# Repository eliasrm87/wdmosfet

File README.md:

# WDSSR

WDSSR is a low side DC Mosfet based SSR board designed to drive resistive loads with and integrated watchdog able to detect some of the more common faults, report and protect it self from fire hazard.

## Watchdog capabilities

The integrated, fully analog, free of firmware, watchdog has the ability to detect:
 - Broken cable
 - Shorted switching Mosfet

For any of the cases described above, the board will “open” the series safety Mosfet and will trigger an alarm open collector signal for the control system to take further action, reducing the fire hazard resulting from an uncontrolled thermal runaway or defective wiring.

## Simplified principle of operation

 - The resistive load pulls the Drain to VCC
 - When Control is pulled up, the MOSFET “closes”, pulling its Drain close GND
 - Comparing voltages at Drain and Gate, a faulty MOSFET can be detected

| Gate | Drain | Result                                 |
| ---- | ----- | -------------------------------------- |
| Low  | Low   | Faulty - Source and drain  shorted     |
| High | Low   | Normal - ON                            |
| Low  | High  | Normal - OFF                           |
| High | High  | Faulty – Open or gate shorted to drain |

## Bill Of Material

You could consider using the included [Interactive Bill of Material](https://htmlpreview.github.io/?https://raw.githubusercontent.com/eliasrm87/wdssr/master/bom/WDSSR_ibom.html) for a better assembly experience.

|Qty|Reference(s)              |Value           |Part Number                                               |LCSC Part #                                                                  |
|---|--------------------------|----------------|----------------------------------------------------------|-----------------------------------------------------------------------------|
|1  |C1                        |100n            |                                                          |C14663                                                                       |
|1  |C2                        |1u              |                                                          |C15849                                                                       |
|1  |C3                        |10n             |                                                          |C14663                                                                       |
|1  |D1                        |ABS6            |                                                          |C169532                                                                      |
|2  |D2, D4                    |BAV70           |                                                          |C68978                                                                       |
|1  |D3                        |LED_G           |                                                          |C72043                                                                       |
|1  |D5                        |LED_R           |                                                          |C2286                                                                        |
|1  |D6                        |D_Zener         |MM3Z12VB                                                  |C891576                                                                      |
|1  |J1                        |B2B-XH-A(LF)(SN)|B3B-XH-AM(LF)(SN)                                         |C161870                                                                      |
|1  |J2                        |1714968         |1714968                                                   |C95692                                                                       |
|1  |J3                        |Conn_01x02_Male |                                                          |C160332                                                                      |
|2  |Q1, Q2                    |IRFR7440TRPBF   |IRFR7440TRPBF                                             |C97244                                                                       |
|2  |Q3, Q4                    |BC846B,215      |                                                          |C87062                                                                       |
|2  |R1, R12                   |2K              |                                                          |C21190                                                                       |
|6  |R2, R5, R11, R14, R15, R16|10K             |                                                          |C25804                                                                       |
|5  |R3, R7, R8, R9, R13       |100K            |                                                          |C25803                                                                       |
|1  |R4                        |1K              |                                                          |C21190                                                                       |
|2  |R6, R17                   |100             |                                                          |C22775                                                                       |
|1  |U1                        |LM358DT         |                                                          |C9418                                                                        |
|1  |U2                        |TLP185          |                                                          |C7240                                                                        |

## Limitations

This design is not bullet proof and may fail to achieve it’s objective in certain cases:
 - The series safety Mosfet may overheat and fail exactly at the same time as the switching Mosfet
 - It is only tested and verified to work with resistive loads, like heaters. Uses of this design with inductive loads has not been yet tested and may need hardware modifications

### Front

### Back

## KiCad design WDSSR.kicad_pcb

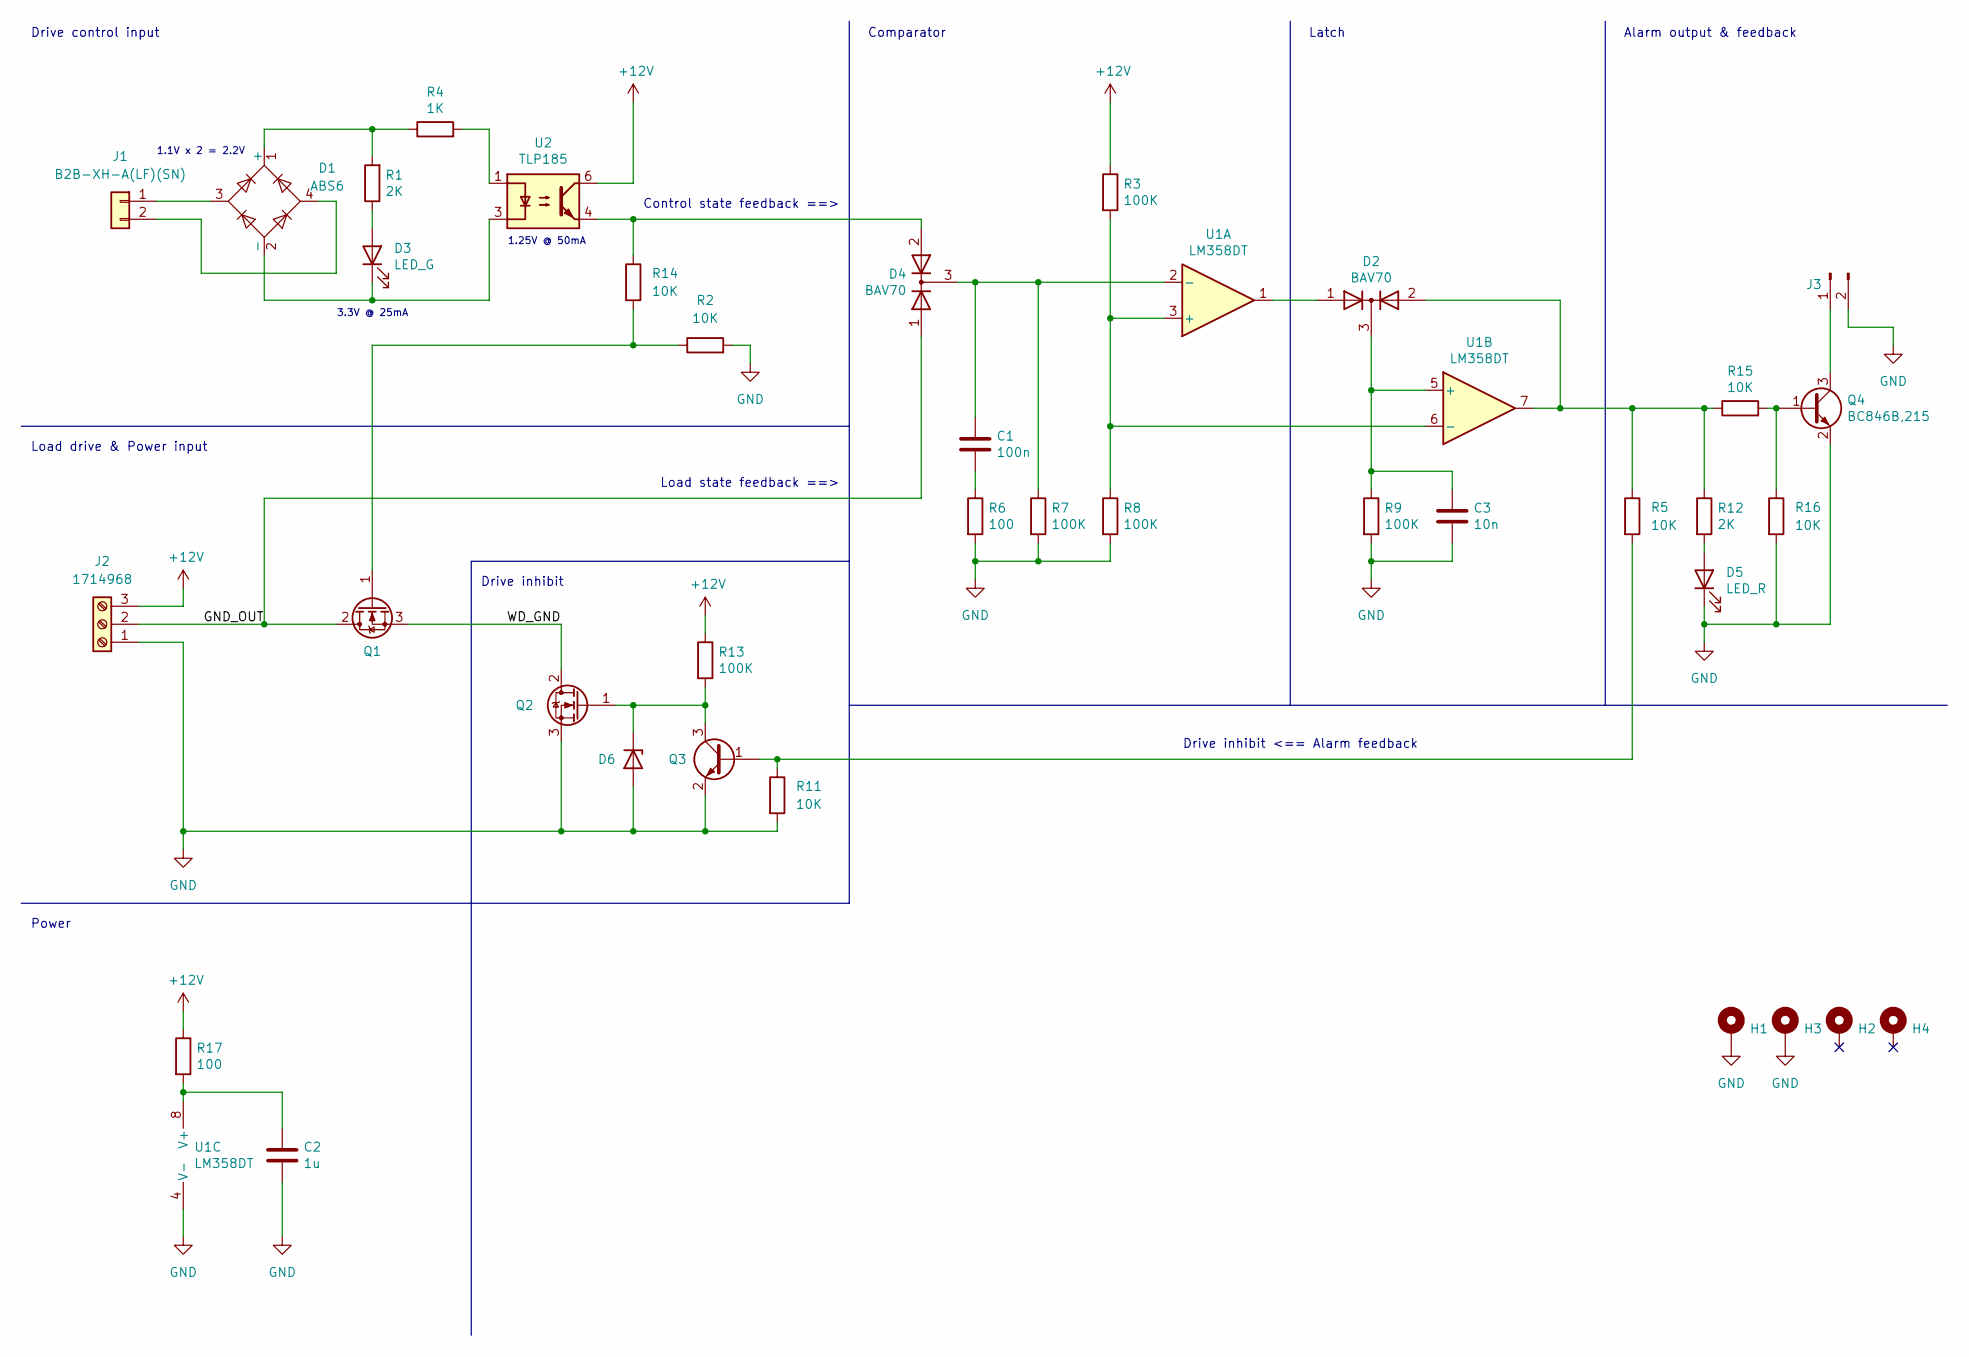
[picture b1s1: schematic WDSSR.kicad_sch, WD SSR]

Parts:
C1: 100n; C_0603_1608Metric_Pad1.08x0.95mm_HandSolder; Manufacturer_Part_Number CC0603KRX7R9BB104; LCSC Part # C14663
C2: 1u; C_0603_1608Metric_Pad1.08x0.95mm_HandSolder; Manufacturer_Part_Number CL10A105KB8NNNC; LCSC Part # C15849
C3: 10n; C_0603_1608Metric_Pad1.08x0.95mm_HandSolder; Manufacturer_Part_Number CC0603KRX7R9BB104; LCSC Part # C14663
D1: ABS6; Diode_Bridge_Diotec_ABS; Manufacturer_Part_Number ABS6-10; LCSC Part # C169532
D2, D4: BAV70; SOT-23; Manufacturer_Part_Number BAV70; LCSC Part # C68978
D3: LED_G; LED_0603_1608Metric_Pad1.05x0.95mm_HandSolder; Manufacturer_Part_Number 19-217/GHC-YR1S2/3T; LCSC Part # C72043
D5: LED_R; LED_0603_1608Metric_Pad1.05x0.95mm_HandSolder; Manufacturer_Part_Number KT-0603R; LCSC Part # C2286
D6: D_Zener; D_SOD-323F; Part Number MM3Z12VB; LCSC Part # C891576
H1, H2, H3, H4: MountingHole; MountingHole_3.2mm_M3_ISO7380_Pad; Manufacturer_Part_Number DNP
J1: B2B-XH-A(LF)(SN); LIB_B2B-XH-A(LF)(SN); Part Number B3B-XH-AM(LF)(SN); LCSC Part # C161870
J2: 1714968; SHDR3W90P0X635_1X3_1905X1250X2150P; Part Number 1714968; LCSC Part # C95692
J3: Conn_01x02_Male; PinHeader_1x02_P2.54mm_Vertical; Manufacturer_Part_Number RE-H022TD-1190(LF)(SN); LCSC Part # C160332
Q1, Q2: IRFR7440TRPBF; TO-252-2; Part Number IRFR7440TRPBF; LCSC Part # C97244
Q3, Q4: BC846B,215; SOT-23; Manufacturer_Part_Number BC846B,215; LCSC Part # C87062
R1, R12: 2K; R_0603_1608Metric_Pad0.98x0.95mm_HandSolder; Manufacturer_Part_Number 0603WAF2001T5E; LCSC Part # C21190
R2, R5, R11, R14, R15, R16: 10K; R_0603_1608Metric_Pad0.98x0.95mm_HandSolder; Manufacturer_Part_Number 0603WAF1002T5E; LCSC Part # C25804
R3, R7, R8, R9, R13: 100K; R_0603_1608Metric_Pad0.98x0.95mm_HandSolder; Manufacturer_Part_Number 0603WAF1003T5E; LCSC Part # C25803
R4: 1K; R_0603_1608Metric_Pad0.98x0.95mm_HandSolder; Manufacturer_Part_Number 0603WAF1001T5E; LCSC Part # C21190
R6, R17: 100; R_0603_1608Metric_Pad0.98x0.95mm_HandSolder; Manufacturer_Part_Number 0603WAF1000T5E; LCSC Part # C22775
U1: LM358DT; SO-8_3.9x4.9mm_P1.27mm; Manufacturer_Part_Number LM358DT; LCSC Part # C9418
U2: TLP185; SOIC-4_4.55x3.7mm_P2.54mm; Manufacturer_Part_Number TLP185(GB-TPL,SE(T; LCSC Part # C7240

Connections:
+12V: J2.3, R3.1, R13.1, R17.1, U2.6
/GND_OUT: D4.1 (A), J2.2, Q1.2 (D)
/WD_GND: Q1.3 (S), Q2.2 (D)
GND: C2.2, C3.2, D5.1 (K), D6.2 (A), H1.1, H3.1, J2.1, J3.2, Q2.3 (S), Q3.2 (E), Q4.2 (E), R2.2, R6.2, R7.2, R8.2, R9.2, R11.2, R16.2, U1.4 (V-)
unnamed: C1.1, D4.3 (K), R7.1, U1.2 (-)
unnamed: C1.2, R6.1
unnamed: C2.1, R17.2, U1.8 (V+)
unnamed: C3.1, D2.3 (K), R9.1, U1.5 (+)
unnamed: D1.1 (+), R1.2, R4.1
unnamed: D1.2 (-), D3.1 (K), U2.3
unnamed: D1.3, J1.1
unnamed: D1.4, J1.2
unnamed: D2.1 (A), U1.1
unnamed: D3.2 (A), R1.1
unnamed: D5.2 (A), R12.2
unnamed: J3.1, Q4.3 (C)
unnamed: D6.1 (K), Q2.1 (G), Q3.3 (C), R13.2
unnamed: Q4.1 (B), R15.2, R16.1
unnamed: R3.2, R8.1, U1.3 (+), U1.6 (-)
unnamed: R4.2, U2.1
unnamed: D2.2 (A), R5.1, R12.1, R15.1, U1.7
unnamed: Q3.1 (B), R5.2, R11.1
unnamed: D4.2 (A), R14.1, U2.4
unnamed: Q1.1 (G), R2.1, R14.2

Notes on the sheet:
Drive control input
Load state feedback ==>
Comparator
Control state feedback ==>
1.1V x 2 = 2.2V
Power
Alarm output & feedback
Drive inhibit
Drive inhibit <== Alarm feedback
1.25V @ 50mA
Load drive & Power input
Latch
3.3V @ 25mA

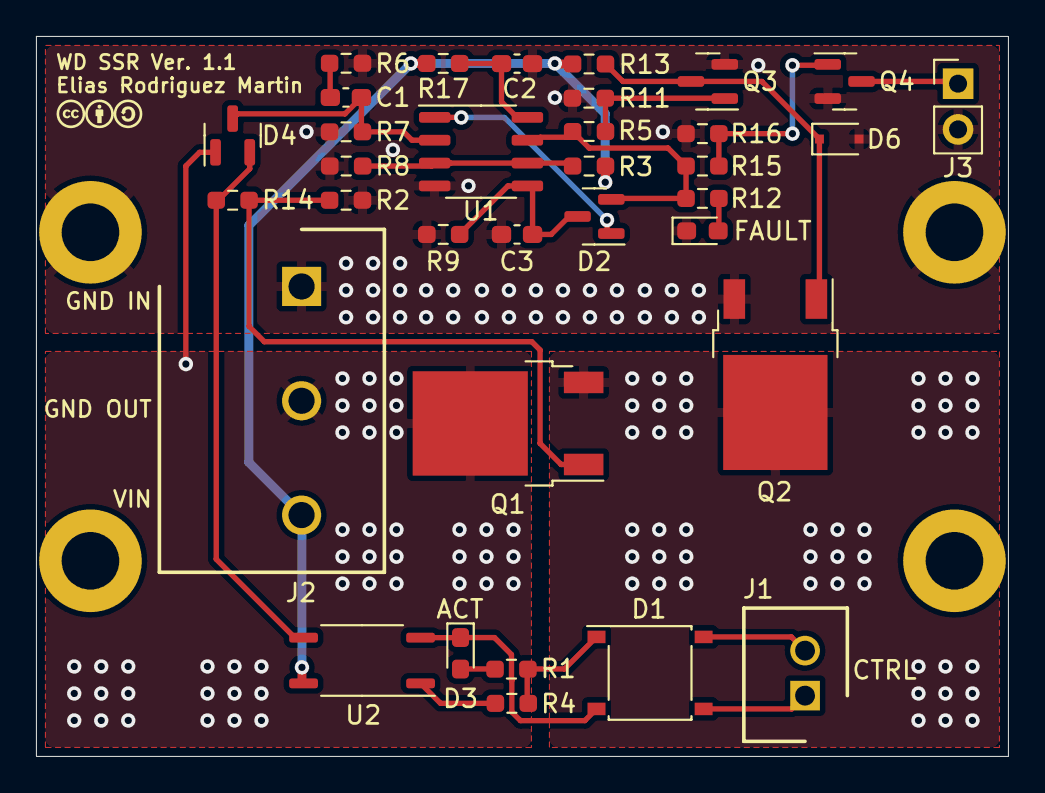
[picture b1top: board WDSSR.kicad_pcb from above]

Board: 2 copper layers, 54.0 x 40.0 mm, 39 parts (0 on the bottom side), 24 nets.

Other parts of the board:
kibuzzard-6340B178: G***; kibuzzard-6340B178

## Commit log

2022-11-06 Add BoM to README
